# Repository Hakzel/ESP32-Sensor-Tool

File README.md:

# ESP32-Sensor-Tool
updated version of the ESP-Sensor-Tool which is now working on an ESP32

use different sensors with the ESP32 and control them using a web interface

All sensors can be connected via I2C to the ESP. The SD Card is connected via SPI.

Below you see the main unit, which is controlling the sensors via i2c bus.

It is attached to a power bank via a pin connector in order to use it without a wall plug.

I added the eagle shematics of the main so you can get an idea of how the main unit is connected to the sensors.

All sensors are simply connected via i2c over the RJ45 headers on both partners

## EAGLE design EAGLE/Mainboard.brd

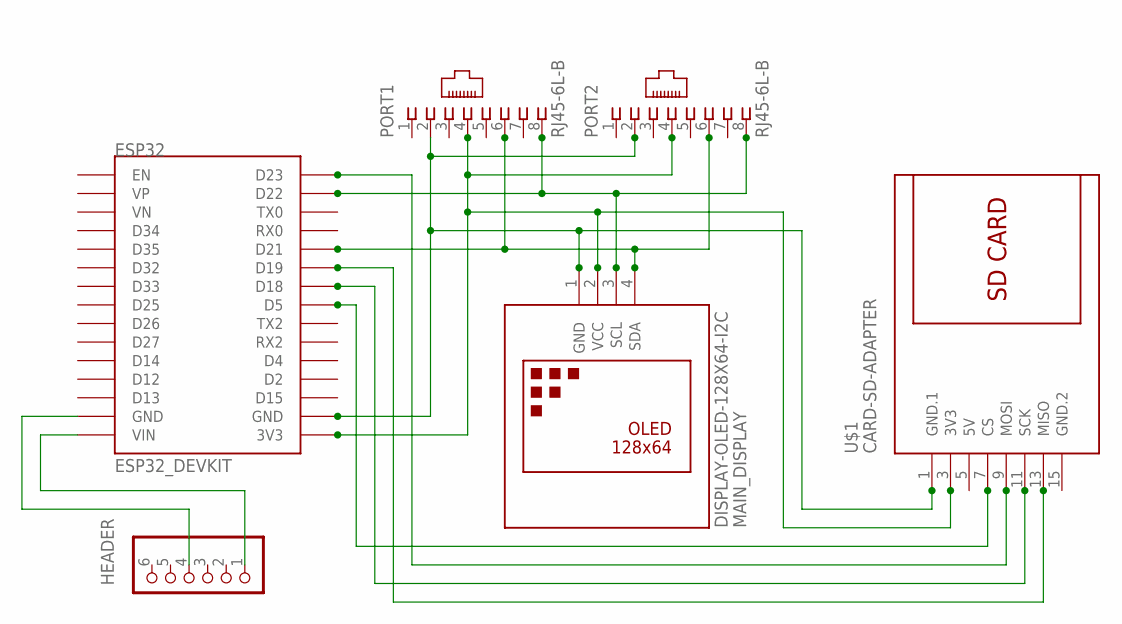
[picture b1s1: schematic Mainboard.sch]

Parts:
ESP32: ESP32_DEVKIT
HEADER: PINHD-1X6CLEAN; 1X06-CLEAN
MAIN_DISPLAY: DISPLAY-OLED-128X64-I2C
PORT1, PORT2: RJ45-6L-B; RJ45-NO-SHIELD
U$1: CARD-SD-ADAPTER

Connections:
5V: U$1.5 (5V)
GND.2: U$1.15 (GND.2)
unnamed: ESP32.D21, MAIN_DISPLAY.4 (SDA), PORT1.6, PORT2.6
unnamed: ESP32.D23, U$1.9 (MOSI)
unnamed: ESP32.D22, MAIN_DISPLAY.3 (SCL), PORT1.8, PORT2.8
unnamed: ESP32.D18, U$1.11 (SCK)
unnamed: ESP32.D5, U$1.7 (CS)
unnamed: ESP32.D19, U$1.13 (MISO)
unnamed: ESP32.GND@2 (GND), MAIN_DISPLAY.1 (GND), PORT1.2, PORT2.2, U$1.1 (GND.1)
unnamed: ESP32.VIN, HEADER.1
unnamed: ESP32.3V3, MAIN_DISPLAY.2 (VCC), PORT1.4, PORT2.4, U$1.3 (3V3)
unnamed: ESP32.GND@1 (GND), HEADER.4

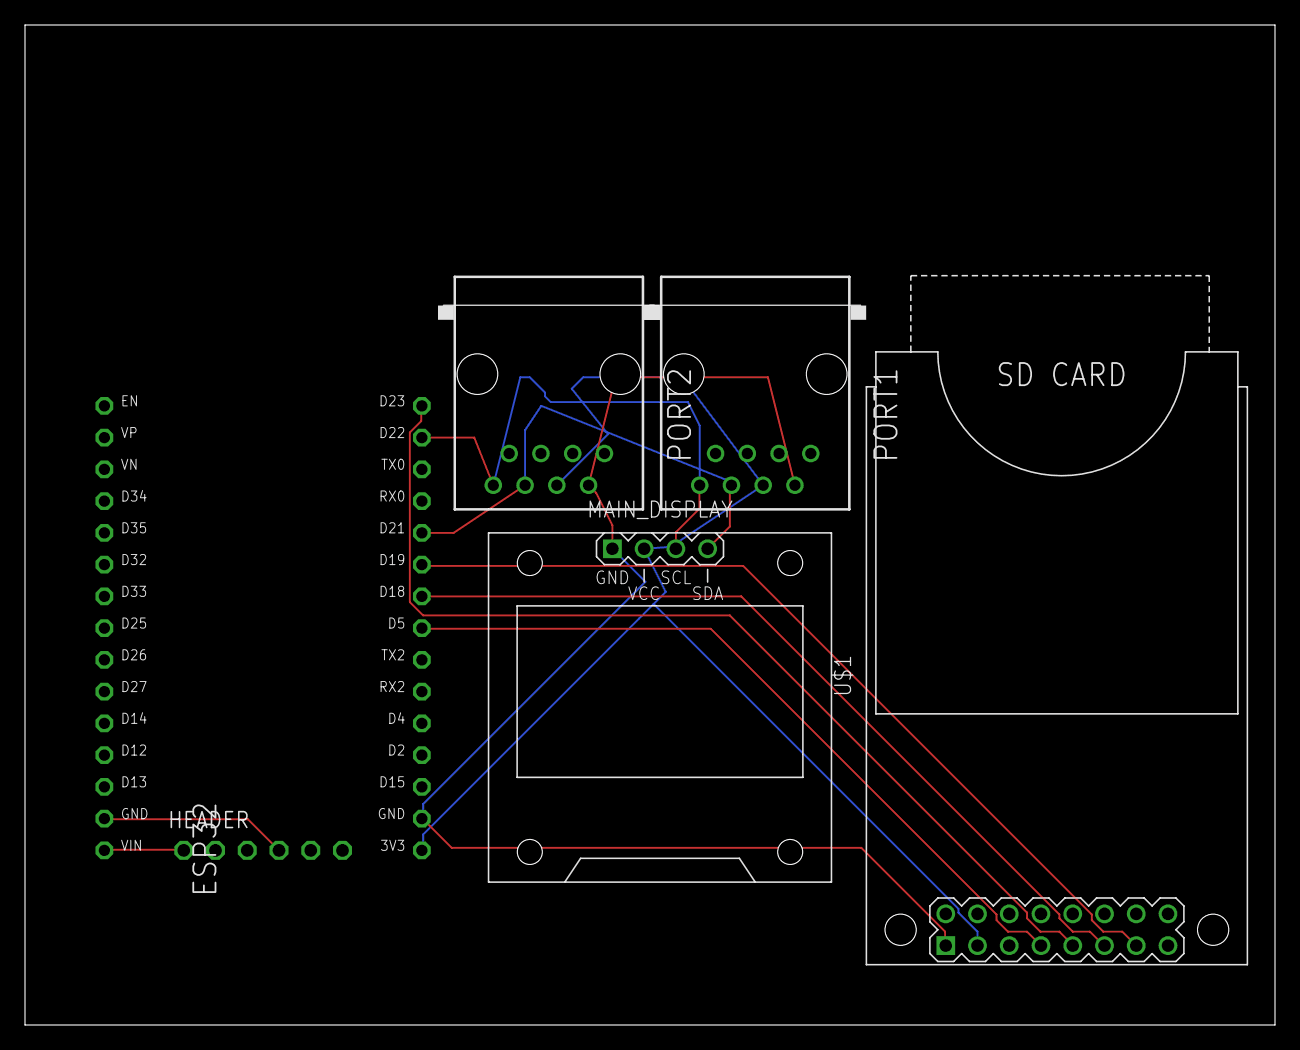
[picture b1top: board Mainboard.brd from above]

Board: 2 copper layers, 100.0 x 80.0 mm, 6 parts (0 on the bottom side), 10 nets.

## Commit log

2018-12-03 Create testfile
2018-12-19 Add files via upload
    Updated Version of the Sensor-Tool using ajax javascript for updating the content on the controlpage

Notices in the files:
parts and their libraries:
diy-modules: Released under the Creative Commons Attribution 4.0 International License: http://creativecommons.org/licenses/by/4.0
